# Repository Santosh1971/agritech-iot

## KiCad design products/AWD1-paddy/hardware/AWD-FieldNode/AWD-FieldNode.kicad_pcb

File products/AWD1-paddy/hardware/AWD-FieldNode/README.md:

# AWD field node v0.3: segmented capacitive level strip on a 2-layer board

This board is the paddy AWD (alternate wetting and drying) field node. It is a T-shaped, **2-layer** PCB (v0.1 was 4 layers).

- **Head:** 40 × 60 mm, inside a sealed 50 mm PVC end cap.
  - **Front:** ESP32-S3-MINI-1, ISC-SX1262-B LoRa module (same module and pin map as WPC), SMA, the touch series resistors.
  - **Back:** power: battery connector J3 (LiFePO4 14500), magnetic-socket connector J4, charger, LDO, fuse, reverse protection, USB ESD.
- **Strip:** 16 × 300 mm, pushed into the AWD tube.
  - 12 sensing pads, 6 × 18 mm on a 20 mm pitch, covering +7 to −17 cm, plus a dry reference pad (REF) above them.
  - One 12 × 20 mm GND water-return pad at the bottom.

The node reports to a WPC-style Master over LoRa at 866 MHz.

## Why 2 layers works for the strip

| Layer | What is on it |
|---|---|
| F.Cu | Pads in the left column. On the right, a **staircase** of 0.15 mm sense lanes, each between two 0.15 mm **GND guard traces** (0.15 mm gaps). Each lane runs straight down and steps left into its pad; the guard on its left ends just above that pad in a via to the back GND. |
| B.Cu | GND: 25 % hatch behind the pads, solid behind the lanes. No routing allowed on the back of the strip. |

- **Water rises from the bottom, and every lane runs only above its own pad.** A pad is always wet before any part of its own lane is, so water touching a lane can only make an already-wet pad read wetter.
- **The guards stop crosstalk** between a wet lower pad's lane and a dry higher pad's lane, the job the inner GND planes did in v0.1.
- **Cost:** a 2-layer board, HASL finish and no impedance control costs roughly a third to a half of the 4-layer ENIG board (estimate, check the quote).
- **To verify on the bench before the field:** in a water tube, check that a dry pad's reading does not move when the pads below it go under water.

The v0.1 4-layer board and its Gerbers are kept in `archive/v0.1-4layer/` for comparison.

## Status (v0.3, 2026-11-15)

| Item | State |
|---|---|
| Schematic | v0.3: v0.2 field charging + new touch-channel order. 66 parts. **ERC: 0 errors, 0 warnings.** |
| PCB | Generated by `tools/build.sh` (placement, strip, Freerouting, GND stitching, silkscreen). **DRC at every severity: 0 violations, 0 unconnected, schematic parity clean** (kicad-cli 9.0.7). |
| Fab | `fab/`: Gerbers + drills (`AWD-FieldNode-gerbers.zip`, **order this**), BOM, CPL (both sides), schematic PDF, 1:1 prints of top and bottom, STEP, renders. Regenerate with `zsh tools/fab.sh`. |
| Enclosure | Strip slot and gland widened for the 16 mm strip (`enclosure/awd_enclosure.scad`, STLs re-exported). |
| Open | The front-shell light window only sits over D1 (status LED). D2/D3 (charge LEDs) are 3.5–7 mm to its right: widen the window, or move them, when the magnetic-socket hole is added to the shell. J3 (battery) is now on the back-right corner, so the AA-holder lead runs there. |

### Changes from v0.1/v0.2

- 4 layers → 2 layers; strip 10 → 16 mm; pads 8 → 6 mm wide; ENIG → HASL.
- **The touch bus is drawn by the generator, not the autorouter:** each ESP32 touch pin goes through a via to B.Cu, runs as a ladder straight down under the LoRa module (F.Cu above it is a solid GND pour), and steps back up into its 510 Ω resistor. Channels follow the pads, so nothing crosses: **REF = T13/IO13, P1 = T12/IO12 … P12 = T1/IO1. Firmware must use this map.**
- **SMA J1:** v0.1 placed it with its pads running 1.4 mm past the board edge. In the footprint the connector body face is where the pads end (2.54 mm from the origin), so v0.3 puts the pad ends 0.3 mm inside the edge.
- The power block moved to the back so the 13 touch traces have the front-left corner of the head to themselves.
- No top-layer tracks under the LoRa module: F.Cu there is solid GND under the radio, and only the touch bus passes, on B.Cu below that pour. The battery connector J3 moved to the back-right corner to make room. No tracks or vias within 0.6 mm of the head edges.
- Antenna feed: 1.0 mm grounded coplanar line, 0.2 mm gap to the F.Cu pour, solid GND behind. It is about 11 mm long (λ/16 at 866 MHz in FR4), so no impedance control is ordered.

## Pin map (ESP32-S3)

| Function | GPIO |
|---|---|
| Touch T13 → REF pad | IO13 |
| Touch T12 → P1, T11 → P2 … T1 → P12 (Pn = IO(13 − n)) | IO12 … IO1 |
| VBUS_DET (charger present, deep-sleep wake), to TP1 | IO14 |
| VBAT_ADC (ADC2_CH4) / VBAT_EN | IO15 / IO16 |
| LoRa DIO1 / BUSY / RST | IO17 / IO18 / IO21 |
| LoRa NSS / SCK / MOSI / MISO | IO39 / IO40 / IO41 / IO42 |
| LED | IO38 |
| PAIR/BOOT button | IO0 |
| USB D−/D+ and UART0 | J2 (1.27 mm pogo/header) |

## v0.2 power: charging in the field through a magnetic socket

v0.1 put the 14500 straight onto the 3V3 rail with no charger, so the box had to be opened to charge the cell. v0.2 adds the same charging block as TH2:

```
J4 magnetic socket (VBUS, D-, D+, GND) -> F1 0.5 A polyfuse -> VBUS -> U3 CN3058E (0.31 A, 3.6 V CV) -> VBAT
J3 14500 -> Q1 reverse protection -> VBAT -> U4 RT9080-33 (2 uA Iq) -> +3V3
```

- **The LDO is now required:** while charging, VBAT sits at 3.6 V, which is the ESP32-S3's absolute maximum.
- **Battery sense:** R4 now measures **VBAT** (before the LDO), not +3V3.
- **USB:** J4's D−/D+ join the native-USB lines already on J2, through U5 (USBLC6 ESD protection). The node can be flashed through the magnetic cable without opening the box.
- **Charge LEDs:** D2 red (charging) and D3 green (full) run off VBUS. Place them under, or next to, the front-shell light window.
- **Charger detect:** VBUS_DET (R12/R13 divider to IO14, an RTC GPIO) wakes the S3 when the cable is clipped on.
- **Enclosure:** the magnetic socket needs its own wall hole, because the side hole is used by the SMA. That waits until the socket's flange size is known (ElectronifyIndia 4-pin flanged for prototypes, HytePro M826 waterproof for production). It goes in the shared AWD/TH shell.

## AWD thresholds

| Action | Condition |
|---|---|
| Pump OFF (+5 cm) | P2 wet |
| Pump ON (−15 cm) | P11 dry |
| SOIL line (0 cm) | Printed on both faces as the installation depth mark |

## Regenerate

Everything is generated from `tools/design.py` (parts, nets, strip geometry).

```bash
cd products/AWD1-paddy/hardware/AWD-FieldNode
zsh tools/build.sh      # schematic + ERC, board, Freerouting (retried until DRC is clean), stitching, silkscreen
zsh tools/fab.sh        # fab/: gerbers, drills, BOM, CPL, PDFs, STEP, renders
```

`build.sh` rebuilds the board from scratch every time, so any hand edits in KiCad are lost: make changes in `design.py` / `gen_pcb.py` instead. Freerouting 1.9.0 is expected at `~/Applications/freerouting/freerouting-1.9.0.jar`.

## Fab notes

- **2 layers, 1.6 mm FR4, HASL lead-free, green mask both sides, vias tented.** Minimum track/gap 0.15 mm, minimum drill 0.3 mm.
- Parts on **both sides**: power block on the back. For JLC assembly choose two-sided, or hand-solder the back.
- The pads have **no mask opening**. Below the neck the strip carries no exposed copper.
- After assembly, dip-coat the strip in 2-part epoxy or PU, 100–200 µm thick, and seal the routed edges.

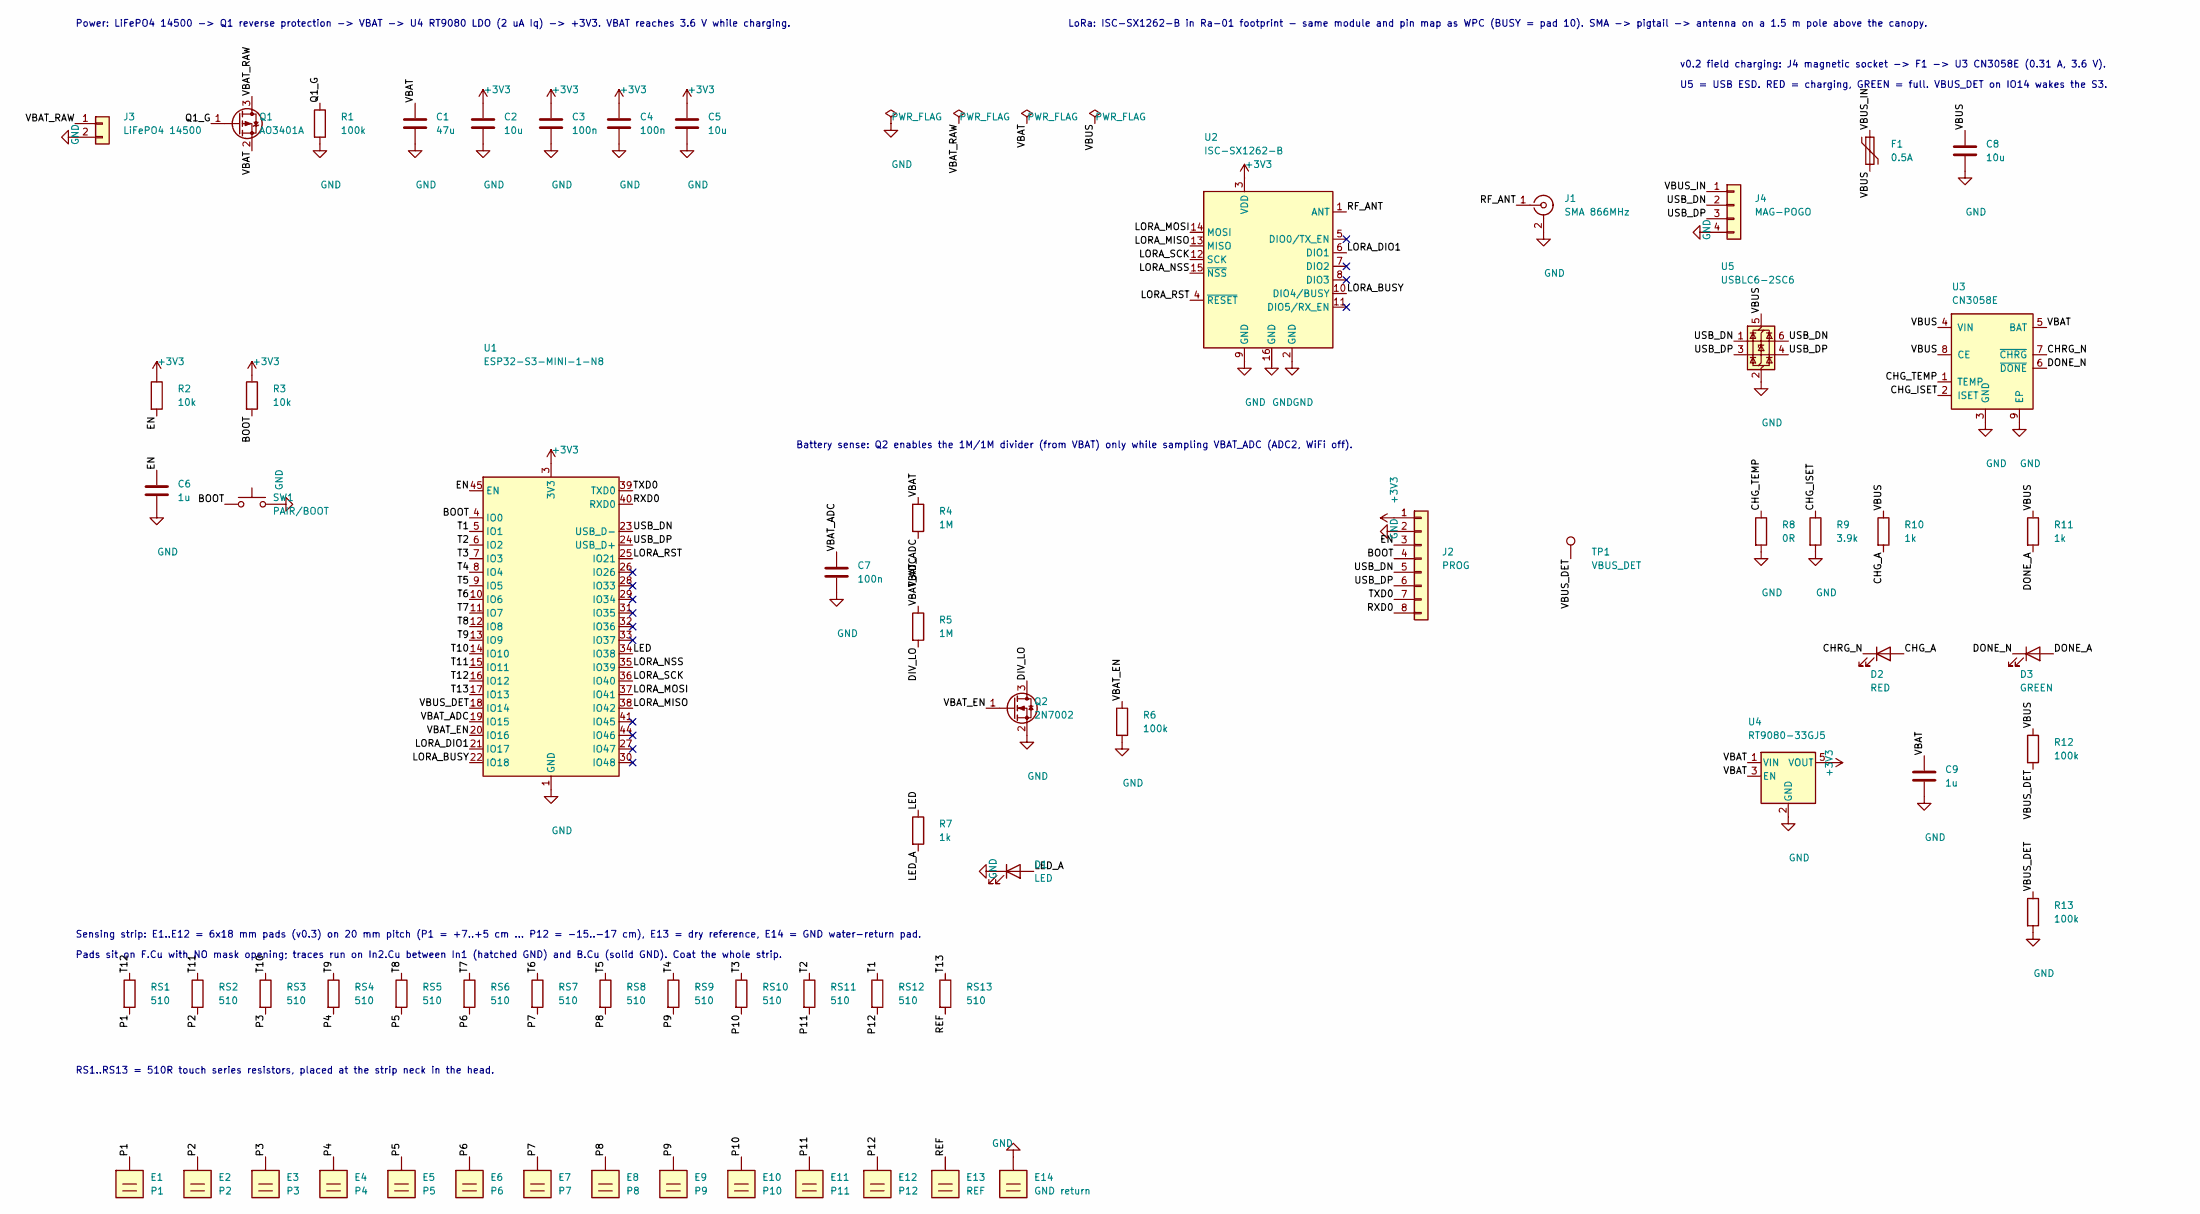
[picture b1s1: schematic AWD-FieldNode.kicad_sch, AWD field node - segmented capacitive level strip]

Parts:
C1: 47u; C_1206_3216Metric
C2, C5, C8: 10u; C_0805_2012Metric
C3, C4, C7: 100n; C_0603_1608Metric
C6, C9: 1u; C_0603_1608Metric
D1: LED; LED_0603_1608Metric
D2: RED; LED_0603_1608Metric
D3: GREEN; LED_0603_1608Metric
E1: P1; SensePad_6x18mm
E2: P2; SensePad_6x18mm
E3: P3; SensePad_6x18mm
E4: P4; SensePad_6x18mm
E5: P5; SensePad_6x18mm
E6: P6; SensePad_6x18mm
E7: P7; SensePad_6x18mm
E8: P8; SensePad_6x18mm
E9: P9; SensePad_6x18mm
E10: P10; SensePad_6x18mm
E11: P11; SensePad_6x18mm
E12: P12; SensePad_6x18mm
E13: REF; SensePad_6x12mm
E14: GND return; ReturnPad_12x20mm
F1: 0.5A; Fuse_1206_3216Metric
J1: SMA 866MHz; SMA_Amphenol_132289_EdgeMount
J2: PROG; PinHeader_1x08_P1.27mm_Vertical
J3: LiFePO4 14500; JST_PH_S2B-PH-SM4-TB_1x02-1MP_P2.00mm_Horizontal
J4: MAG-POGO; JST_PH_S4B-PH-SM4-TB_1x04-1MP_P2.00mm_Horizontal
Q1: AO3401A; SOT-23
Q2: 2N7002; SOT-23
R1, R6, R12, R13: 100k; R_0603_1608Metric
R2, R3: 10k; R_0603_1608Metric
R4, R5: 1M; R_0603_1608Metric
R7, R10, R11: 1k; R_0603_1608Metric
R8: 0R; R_0603_1608Metric
R9: 3.9k; R_0603_1608Metric
RS1, RS2, RS3, RS4, RS5, RS6, RS7, RS8, RS9, RS10, RS11, RS12, RS13: 510; R_0402_1005Metric
SW1: PAIR/BOOT; SW_SPST_TL3342
TP1: VBUS_DET; TestPoint_Pad_D1.5mm
U1: ESP32-S3-MINI-1-N8; ESP32-S2-MINI-1
U2: ISC-SX1262-B; Ai-Thinker-Ra-01-LoRa
U3: CN3058E; SOIC-8-1EP_3.9x4.9mm_P1.27mm_EP2.41x3.3mm
U4: RT9080-33GJ5; SOT-23-5
U5: USBLC6-2SC6; SOT-23-6

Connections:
+3V3: C2.1, C3.1, C4.1, C5.1, J2.1, R2.1, R3.1, U1.3 (3V3), U2.3 (VDD), U4.5 (VOUT)
/BOOT: J2.4, R3.2, SW1.1, U1.4 (IO0)
/CHG_A: D2.2 (A), R10.2
/CHG_ISET: R9.1, U3.2 (ISET)
/CHG_TEMP: R8.1, U3.1 (TEMP)
/CHRG_N: D2.1 (K), U3.7 (~CHRG)
/DIV_LO: Q2.3 (D), R5.2
/DONE_A: D3.2 (A), R11.2
/DONE_N: D3.1 (K), U3.6 (~DONE)
/EN: C6.1, J2.3, R2.2, U1.45 (EN)
/LED: R7.1, U1.34 (IO38)
/LED_A: D1.2 (A), R7.2
/LORA_BUSY: U1.22 (IO18), U2.10 (DIO4/BUSY)
/LORA_DIO1: U1.21 (IO17), U2.6 (DIO1)
/LORA_MISO: U1.38 (IO42), U2.13 (MISO)
/LORA_MOSI: U1.37 (IO41), U2.14 (MOSI)
/LORA_NSS: U1.35 (IO39), U2.15 (~NSS)
/LORA_RST: U1.25 (IO21), U2.4 (~RESET)
/LORA_SCK: U1.36 (IO40), U2.12 (SCK)
/P1: E1.1, RS1.2
/P2: E2.1, RS2.2
/P3: E3.1, RS3.2
/P4: E4.1, RS4.2
/P5: E5.1, RS5.2
/P6: E6.1, RS6.2
/P7: E7.1, RS7.2
/P8: E8.1, RS8.2
/P9: E9.1, RS9.2
/P10: E10.1, RS10.2
/P11: E11.1, RS11.2
/P12: E12.1, RS12.2
/Q1_G: Q1.1 (G), R1.1
/REF: E13.1, RS13.2
/RF_ANT: J1.1 (In), U2.1 (ANT)
/RXD0: J2.8, U1.40 (RXD0)
/T1: RS12.1, U1.5 (IO1)
/T2: RS11.1, U1.6 (IO2)
/T3: RS10.1, U1.7 (IO3)
/T4: RS9.1, U1.8 (IO4)
/T5: RS8.1, U1.9 (IO5)
/T6: RS7.1, U1.10 (IO6)
/T7: RS6.1, U1.11 (IO7)
/T8: RS5.1, U1.12 (IO8)
/T9: RS4.1, U1.13 (IO9)
/T10: RS3.1, U1.14 (IO10)
/T11: RS2.1, U1.15 (IO11)
/T12: RS1.1, U1.16 (IO12)
/T13: RS13.1, U1.17 (IO13)
/TXD0: J2.7, U1.39 (TXD0)
/USB_DN: J2.5, J4.2, U1.23 (USB_D-), U5.1 (I/O1), U5.6 (I/O1)
/USB_DP: J2.6, J4.3, U1.24 (USB_D+), U5.3 (I/O2), U5.4 (I/O2)
/VBAT: C1.1, C9.1, Q1.2 (S), R4.1, U3.5 (BAT), U4.1 (VIN), U4.3 (EN)
/VBAT_ADC: C7.1, R4.2, R5.1, U1.19 (IO15)
/VBAT_EN: Q2.1 (G), R6.1, U1.20 (IO16)
/VBAT_RAW: J3.1, Q1.3 (D)
/VBUS: C8.1, F1.2, R10.1, R11.1, R12.1, U3.4 (VIN), U3.8 (CE), U5.5 (VBUS)
/VBUS_DET: R12.2, R13.1, TP1.1, U1.18 (IO14)
/VBUS_IN: F1.1, J4.1
GND: C1.2, C2.2, C3.2, C4.2, C5.2, C6.2, C7.2, C8.2, C9.2, D1.1 (K), E14.1, J1.2 (Ext), J2.2, J3.2, J4.4, Q2.2 (S), R1.2, R6.2, R8.2, R9.2, R13.2, SW1.2, U1.1 (GND), U1.2 (GND), U1.42 (GND), U1.43 (GND), U1.46 (GND), U1.47 (GND), U1.48 (GND), U1.49 (GND), U1.50 (GND), U1.51 (GND), U1.52 (GND), U1.53 (GND), U1.54 (GND), U1.55 (GND), U1.56 (GND), U1.57 (GND), U1.58 (GND), U1.59 (GND), U1.60 (GND), U1.61 (GND), U1.62 (GND), U1.63 (GND), U1.64 (GND), U1.65 (GND), U2.2 (GND), U2.9 (GND), U2.16 (GND), U3.3 (GND), U3.9 (EP), U4.2 (GND), U5.2 (GND)

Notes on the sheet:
Power: LiFePO4 14500 -> Q1 reverse protection -> VBAT -> U4 RT9080 LDO (2 uA Iq) -> +3V3. VBAT reaches 3.6 V while charging.
LoRa: ISC-SX1262-B in Ra-01 footprint - same module and pin map as WPC (BUSY = pad 10). SMA -> pigtail -> antenna on a 1.5 m pole above the canopy.
Battery sense: Q2 enables the 1M/1M divider (from VBAT) only while sampling VBAT_ADC (ADC2, WiFi off).
v0.2 field charging: J4 magnetic socket -> F1 -> U3 CN3058E (0.31 A, 3.6 V).
U5 = USB ESD. RED = charging, GREEN = full. VBUS_DET on IO14 wakes the S3.
Sensing strip: E1..E12 = 6x18 mm pads (v0.3) on 20 mm pitch (P1 = +7..+5 cm ... P12 = -15..-17 cm), E13 = dry reference, E14 = GND water-return pad.
Pads sit on F.Cu with NO mask opening; traces run on In2.Cu between In1 (hatched GND) and B.Cu (solid GND). Coat the whole strip.
RS1..RS13 = 510R touch series resistors, placed at the strip neck in the head.

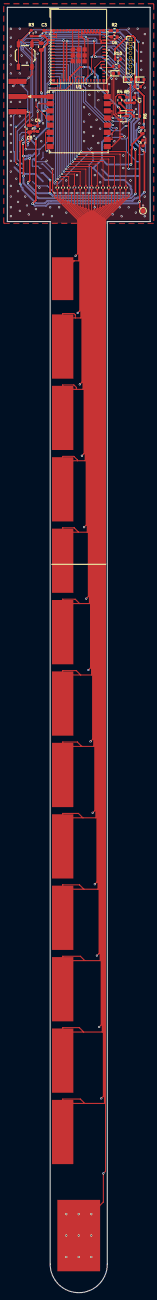
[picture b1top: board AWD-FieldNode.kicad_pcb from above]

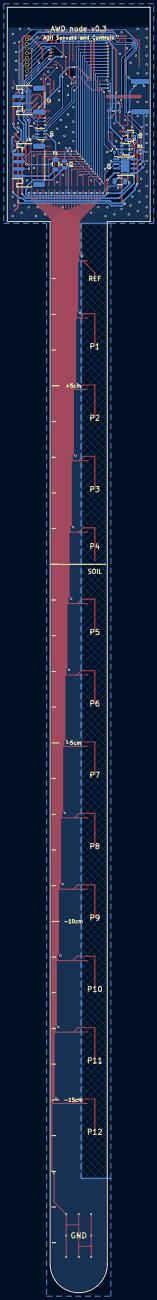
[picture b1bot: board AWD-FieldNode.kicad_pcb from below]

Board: 2 copper layers, 40.0 x 360.0 mm, 66 parts (13 on the bottom side), 59 nets.

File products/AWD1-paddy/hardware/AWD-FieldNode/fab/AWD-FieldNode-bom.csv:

"Reference","Value","Footprint","QUANTITY"
"C1","47u","Capacitor_SMD:C_1206_3216Metric","1"
"C2,C5,C8","10u","Capacitor_SMD:C_0805_2012Metric","3"
"C3,C4,C7","100n","Capacitor_SMD:C_0603_1608Metric","3"
"C6,C9","1u","Capacitor_SMD:C_0603_1608Metric","2"
"D1","LED","LED_SMD:LED_0603_1608Metric","1"
"D2","RED","LED_SMD:LED_0603_1608Metric","1"
"D3","GREEN","LED_SMD:LED_0603_1608Metric","1"
"F1","0.5A","Fuse:Fuse_1206_3216Metric","1"
"J1","SMA 866MHz","Connector_Coaxial:SMA_Amphenol_132289_EdgeMount","1"
"J2","PROG","Connector_PinHeader_1.27mm:PinHeader_1x08_P1.27mm_Vertical","1"
"J3","LiFePO4 14500","Connector_JST:JST_PH_S2B-PH-SM4-TB_1x02-1MP_P2.00mm_Horizontal","1"
"J4","MAG-POGO","Connector_JST:JST_PH_S4B-PH-SM4-TB_1x04-1MP_P2.00mm_Horizontal","1"
"Q1","AO3401A","Package_TO_SOT_SMD:SOT-23","1"
"Q2","2N7002","Package_TO_SOT_SMD:SOT-23","1"
"R1,R6,R12,R13","100k","Resistor_SMD:R_0603_1608Metric","4"
"R2,R3","10k","Resistor_SMD:R_0603_1608Metric","2"
"R4,R5","1M","Resistor_SMD:R_0603_1608Metric","2"
"R7,R10,R11","1k","Resistor_SMD:R_0603_1608Metric","3"
"R8","0R","Resistor_SMD:R_0603_1608Metric","1"
"R9","3.9k","Resistor_SMD:R_0603_1608Metric","1"
"RS1-RS13","510","Resistor_SMD:R_0402_1005Metric","13"
"SW1","PAIR/BOOT","Button_Switch_SMD:SW_SPST_TL3342","1"
"U1","ESP32-S3-MINI-1-N8","RF_Module:ESP32-S2-MINI-1","1"
"U2","ISC-SX1262-B","RF_Module:Ai-Thinker-Ra-01-LoRa","1"
"U3","CN3058E","Package_SO:SOIC-8-1EP_3.9x4.9mm_P1.27mm_EP2.41x3.3mm","1"
"U4","RT9080-33GJ5","Package_TO_SOT_SMD:SOT-23-5","1"
"U5","USBLC6-2SC6","Package_TO_SOT_SMD:SOT-23-6","1"

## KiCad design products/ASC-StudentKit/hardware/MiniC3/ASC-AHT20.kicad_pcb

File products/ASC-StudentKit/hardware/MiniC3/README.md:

# ASC Mini-C3 rev B: the low-cost Mini, shared with FG1

This is the cost-down Mini for the ASC Student Kit (2026-10-10). The same board is meant to become the next **FG1 (FlowGuard)**: it has FG1's flow input, relay, RTC and LEDs. It does not replace rev A (`../Mini`, ESP32-S3 module, 97 × 47 mm).

Two boards share one 100 × 100 order:

| Board | Size | What it is |
|---|---|---|
| **ASC-MiniC3** | 48 × 44 mm | Carrier for a plug-in ESP32-C3 Super Mini. It has a flow input, a 5 V pump driver, a 230 V relay, a DS1307 RTC, I2C and AUX terminals and four LEDs. |
| **ASC-AHT20** | 48 × 6 mm | A T/RH "sensor stick" on a 4-core cable, so the sensor sits outside the box and students can breathe on it |

**The panel (`fab/ASC-MiniC3-panel-gerbers.zip`, 98 × 98 mm, order this one):**
- It holds 4 Minis (2 × 2) and **2 sticks** underneath. FG1 builds don't need a stick.
- **No V-cut.** JLC charges extra for V-cut, so WhyPCB asked for routed slots instead.
- The boards are separated by **2 mm routed slots**, drawn as closed cut-outs in the board outline.
- The slots stop short at the panel edges and around the slot crossings, leaving small **plain tabs**: about 2 mm at the edges and 5 mm at the crossings.
- **No mouse bites:** WhyPCB says JLC may not accept them. To set them back, change `MOUSE_BITES` in `tools/panel.py`. Break the tabs with pliers or a nibbler and file the stubs flush.
- The zip also carries `ASC-MiniC3-panel-drawing.pdf` and `PANEL-README.txt` for the fab.
- Copper keeps ≥ 0.4 mm from every edge.
- **Price** (WhyPCB): ₹1,500 for 5 panels or ₹2,000 for 10, which is ₹50 per Mini at 10 panels. 98 × 98 stays inside their 100 × 100 price; they also accept up to 102 × 100.

## Status

| Item | State |
|---|---|
| Schematics | Both are generated from `tools/design.py` and `tools/design_aht20.py`. **ERC: 0 errors, 0 warnings** on both. |
| PCBs | Both are routed (Freerouting) with zones filled. **DRC at every severity: 0 violations, 0 unconnected, schematic parity clean** on both (kicad-cli 9.0.7). The panel's DRC shows 0 errors. |
| 230 V | **5.3 mm** measured from relay copper to anything else. The DRC rule in `ASC-MiniC3.kicad_dru` requires ≥ 5 mm. Inside the relay, coil and contacts are 9.6 mm apart. |
| Fab | Panel, Mini and stick Gerbers. JLC BOM/CPL for each board and for the panel (unique designators R1_1 … R1_4). Schematic PDFs, 1:1 prints and renders. Run `tools/fab.sh` to regenerate. |
| Costing | `costing.csv`: board plus stick about ₹267, full kit about ₹1,026 (IP-65-26, YF-S401 at ₹230, HF46F at ₹42, 3 standoffs) |
| Mounting | 3 × 4.2 mm holes, arranged in a triangle, for 5 mm nylon reverse-mount snap standoffs (Probots PRO5803, ₹9.40 at 50+). Each standoff's flat base sticks to the box floor with double-sided foam tape; the snap head goes through the PCB hole. This works in any box with a flat floor; the box's own bosses are not used. Enclosure: REI IP-65-26 (90 × 58 × 44). |

## 3D models

Our own parts have no 3D models in KiCad's library (the Phoenix terminals, the MSTBVA header and the JST-XH do). `tools/gen_3d.py` writes simple coloured STEP models for them into `ASC.3dshapes/` (boxes and cylinders sized from the datasheets):
- the Super Mini on its sockets;
- the tabbed CR2032 and the HF46F relay;
- the AHT20 and the snap standoffs (the standoffs show below the board).

`tools/apply_3d.py` attaches them to the routed boards without re-routing; `gen_pcb.py` and `panel.py` attach them automatically. `fab/ASC-MiniC3.step` and `fab/ASC-AHT20.step` are full board assemblies, for checking the fit in the enclosure.

## Pin map (ESP32-C3 Super Mini)

| GPIO | Function | Notes |
|---|---|---|
| IO0, IO1 | AUX A0, A1 | ADC1 inputs |
| IO3 | PUMP | ULN2003A channels 1 + 2 in parallel (about 0.9 V drop, so ~4 V at the pump). Off through reset. |
| IO4 | AUX D | 10 k pull-up. For DHT11/22 or a DS18B20 probe. |
| IO5 | FLOW | YF-S401 (5880 pulses per litre) or YF-S201 (450 per litre). Level-shifted by D2 + R6. |
| IO6, IO7 | SDA, SCL | DS1307 (0x68) and AHT20 (0x38). 4.7 k pull-ups to 3V3. |
| IO10 | STATUS LED | FG1 uses it as the WiFi/status LED |
| IO20 | RELAY | ULN2003A channel 3. This pin is UART0 RX, an input at boot, so the relay stays off while the board boots. ULN2003A inputs 4–7 are grounded, outputs 4–7 free. |
| IO2, IO8, IO9, IO21 | free | IO2/8/9 are strapping pins (IO8 = module LED, IO9 = BOOT). IO21 is UART0 TX. |

## Connectors

| Ref | Connector | Pins |
|---|---|---|
| J5 | I2C, 4-pole 3.5 mm screw terminal (top edge) | 3V3, GND, SCL, SDA. This is the AHT20 stick's order and the usual VIN GND SCL SDA module order. |
| J4 | FLOW (top right): one footprint, fit **either** a JST-XH 3-pin header (student bench: takes the YF-S401 plug) **or** a 3-pole 3.5 mm screw terminal (FG1 / field: long cable). | 5V (red), GND (black), SIG (yellow); silkscreen reads S G 5V, left to right |
| J3 | AUX, 5-pole 3.5 mm screw terminal (bottom edge) | 3V3, D, A0, A1, GND |
| J1 | PUMP, 2-pole 3.5 mm screw terminal (bottom edge) | P+ (5 V), P− (low side) |
| J6 | RELAY 230 V, pluggable 5.08 mm 2-pole MSTBVA header + plug (bottom right), the same family as FG1's relay connector | NO, COM. HF46F, 5 A 250 VAC, for a pump contactor coil. |

## Assembly markings (for hand soldering)

House style, as on the WPC and FG1 boards:
- **Labels:** every part has its reference and value on the top silkscreen: `R3 1K`, `R5 470E`, `U3 ULN2003`, `C1 220U`, `D3 YEL` and so on. R8 and R9 share one label, `R8 R9 4K7`.
- **Big parts:** the relay and coin-cell labels sit inside their outlines, where the part goes.
- **Pin 1:** a **1** marks pin 1 of each IC (U2 DS1307, U3 ULN2003, the AHT20).
- **Anodes:** a **+** marks the anode of every LED and of D2.
- **LED colours:** PUMP and RLY yellow, STATUS red, FLOW yellow-green. FLOW runs from 3.3 V, too low for an emerald green LED. The Super Mini's own blue LED (GPIO8) is the WiFi-status LED in firmware. The electrolytic and the coin cell carry their own + marks.
- **LED size:** the LEDs are **1206** (bigger pads, as on WPC).
- **Back:** "ASC Mini-C3 rev B / Agri Sensors and Controls Oct 2026".

`gen_pcb.py` places the labels automatically, clear of pads, part bodies and each other (`ASSEMBLY_VALUE`, `LABEL_INSIDE` and `MARKS` in the design file). The LED block is laid out by hand in `silk()`.

## LEDs (seen through the clear lid)

| LED | How it's driven |
|---|---|
| PUMP (red) | Hardware: on the pump driver |
| FLOW (yellow) | Hardware: blinks with every flow pulse |
| STATUS (green) | GPIO10 |
| RELAY (blue) | Hardware: across the relay coil |

## Moving FG1 onto this board

1. **Firmware.** FG1 runs on a classic ESP32 today (`esp32dev`). It needs a C3 build with these pins: RELAY IO20, FLOW IO5, I2C IO6/IO7, status LED IO10.
2. **Flow LED.** It no longer needs a GPIO, so FG1's `FLOW_SENSOR_LED_PIN` goes away.
3. **Flow sensor.** Set `DEFAULT_PULSES_PER_LITER` to suit the sensor: 450 for a YF-S201, 5880 for a YF-S401.
4. **Power.** In the field, FG1 runs from a 5 V / 1 A USB-C charger plugged into the Super Mini.
5. **Relay.** The relay is an HF46F (5 A), not FG1's SRD (10 A). That is ample for a contactor coil. The SRD's COM pin sits between its two coil pins, which made 5 mm clearance impossible on a 48 mm board.

## Check before ordering

1. **Super Mini footprint.** Print `fab/ASC-MiniC3-print-1to1.pdf` at 100 % and lay a real Super Mini on it. The rows should be 15.24 mm apart. The silkscreen marks IO5 and 5V at the USB end and IO21 and IO0 at the far end, so a mirrored module is easy to see.
2. **Tabbed CR2032.** The two + legs are 15.2 mm apart. The − leg offset of 4.0 mm is a guess, so measure one cell.
   - **Alternative:** a replaceable cell in a CR2032 holder ([Rajiv Electronics](https://rajivelectronics.com/product/cr2032-3v-pcb-mount-vertical-battery-holder), ₹11.80).
   - The Rajiv holder (photo, SKU RBH-2) is a vertical holder with **3 pins**. A different holder's datasheet shows 2 pins 20.0 mm apart, so the layout varies by maker.
   - Its pin positions may or may not match the tabbed cell's pads. **Measure a sample before ordering.**
   - If they differ, its pads can be added next to the tabbed cell's, the same way the flow connector takes either part.
3. **YF-S401 plug order.** The board expects 5V (red) on pin 1, GND (black) in the middle and SIG (yellow) on pin 3. This follows AM Electronics' listing and photo. Check one plug: red must land on the pin next to the 5V label.
4. **HF46F footprint.** It is the same footprint as rev A (Hongfa datasheet). Push a real relay through a 1:1 print.
5. **AHT20 footprint.** It follows the ASAIR datasheet V1.0.03, figure 8: 0.8 × 0.5 mm pads at 1.0 mm pitch, rows 2.0 mm apart. Pins: 2 VDD, 3 SCL, 4 SDA, 5 GND.
6. **Assembly on the panel.** JLC assembly normally wants 5 mm rails, which would make the panel 96 × 110 mm. Either assemble by hand (every passive is 0805; the AHT20 needs hot air or a stencil) or ask WhyPCB whether they can place parts on a panel with no rails.
7. **USB power.** The pump (0.2–0.3 A), the relay coil (~70 mA) and the C3 (up to ~350 mA) all run from USB 5 V. Use a 1 A charger.

## Regenerate

```bash
cd products/ASC-StudentKit/hardware/MiniC3
KP=/Applications/KiCad/KiCad.app/Contents/Frameworks/Python.framework/Versions/Current/bin/python3
for d in design design_aht20; do
  DESIGN=$d python3 tools/gen_sch.py      # schematic, ASC.kicad_sym, tools/netlist-<PROJECT>.json
  DESIGN=$d $KP tools/gen_pcb.py          # placed board (plus the locked 230 V tracks)
  DESIGN=$d $KP tools/route.py            # Freerouting 1.9 (~/Applications/freerouting), then zone fill
done
kicad-cli pcb drc --schematic-parity --severity-all -o /tmp/drc.rpt ASC-MiniC3.kicad_pcb
$KP tools/panel.py                        # panel/ASC-MiniC3-panel.kicad_pcb
zsh tools/fab.sh                          # fab/
```

Freerouting is not deterministic. If DRC reports unconnected items, run `gen_pcb.py` and `route.py` again; a clean result usually comes within a few runs.

How the routing script handles the special nets:
- The two 230 V tracks are drawn and locked by `gen_pcb.py`. Freerouting cannot place them, because the terminal's own pins are closer together than the 5 mm class clearance.
- The GND pours are taken out of the DSN export, so GND is also routed as tracks.
- The no-pour areas are taken out of the export too, because the exporter would turn them into full keep-outs.

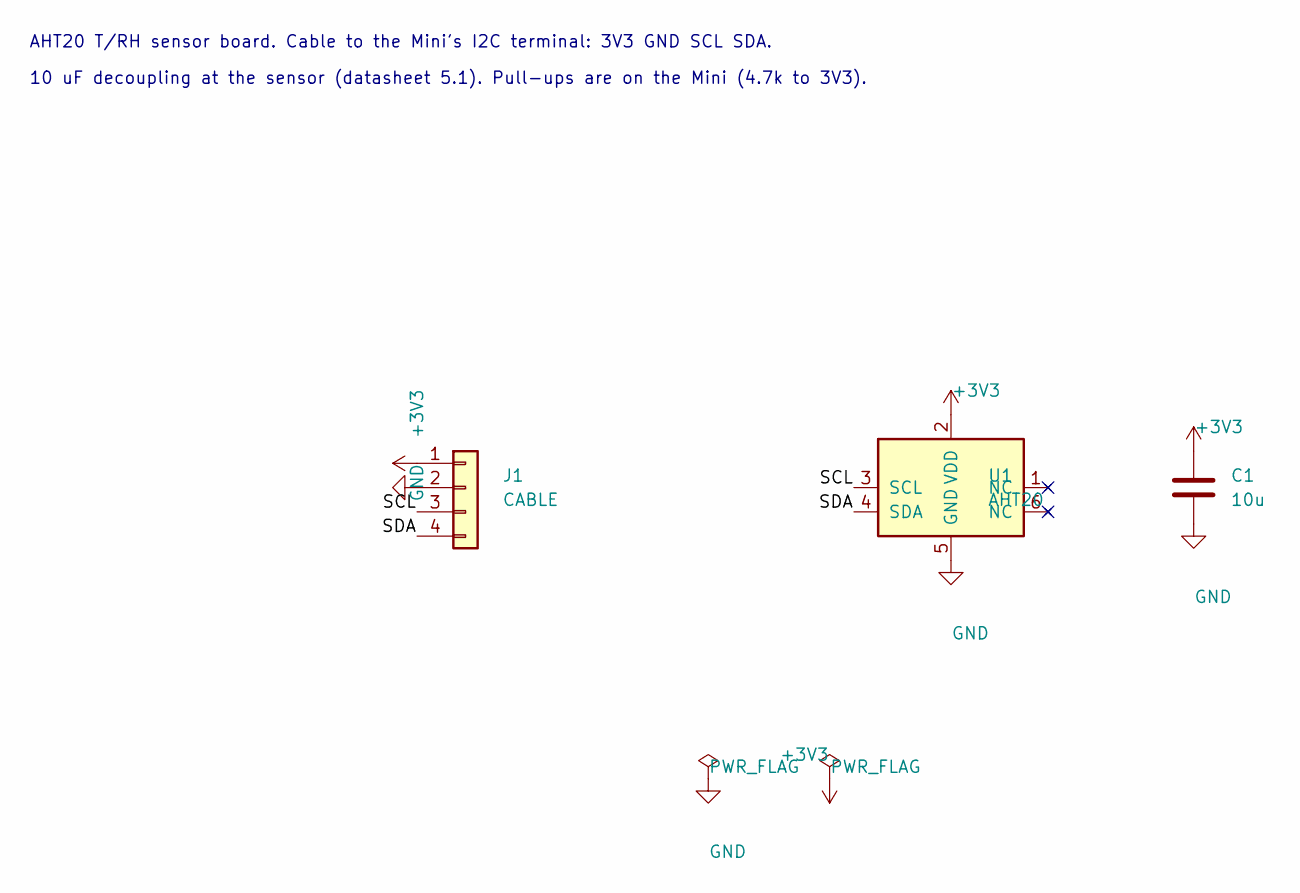
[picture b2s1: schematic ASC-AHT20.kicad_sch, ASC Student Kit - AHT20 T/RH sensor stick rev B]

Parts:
C1: 10u; C_0805_2012Metric
J1: CABLE; PinHeader_1x04_P2.54mm_Vertical
U1: AHT20; Aosong_AHT20_DFN-6_3x3mm

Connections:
+3V3: C1.1, J1.1, U1.2 (VDD)
/SCL: J1.3, U1.3 (SCL)
/SDA: J1.4, U1.4 (SDA)
GND: C1.2, J1.2, U1.5 (GND)

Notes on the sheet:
AHT20 T/RH sensor board. Cable to the Mini's I2C terminal: 3V3 GND SCL SDA.
10 uF decoupling at the sensor (datasheet 5.1). Pull-ups are on the Mini (4.7k to 3V3).

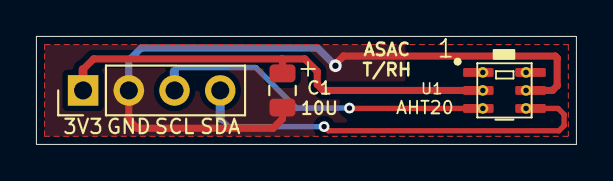
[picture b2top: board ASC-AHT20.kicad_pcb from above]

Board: 2 copper layers, 30.0 x 6.0 mm, 3 parts (0 on the bottom side), 4 nets.

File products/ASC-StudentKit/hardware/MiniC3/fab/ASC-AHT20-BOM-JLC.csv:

Comment,Designator,Footprint,LCSC Part #
10u,C1,C_0805_2012Metric,C15850
AHT20,U1,Aosong_AHT20_DFN-6_3x3mm,C2757850

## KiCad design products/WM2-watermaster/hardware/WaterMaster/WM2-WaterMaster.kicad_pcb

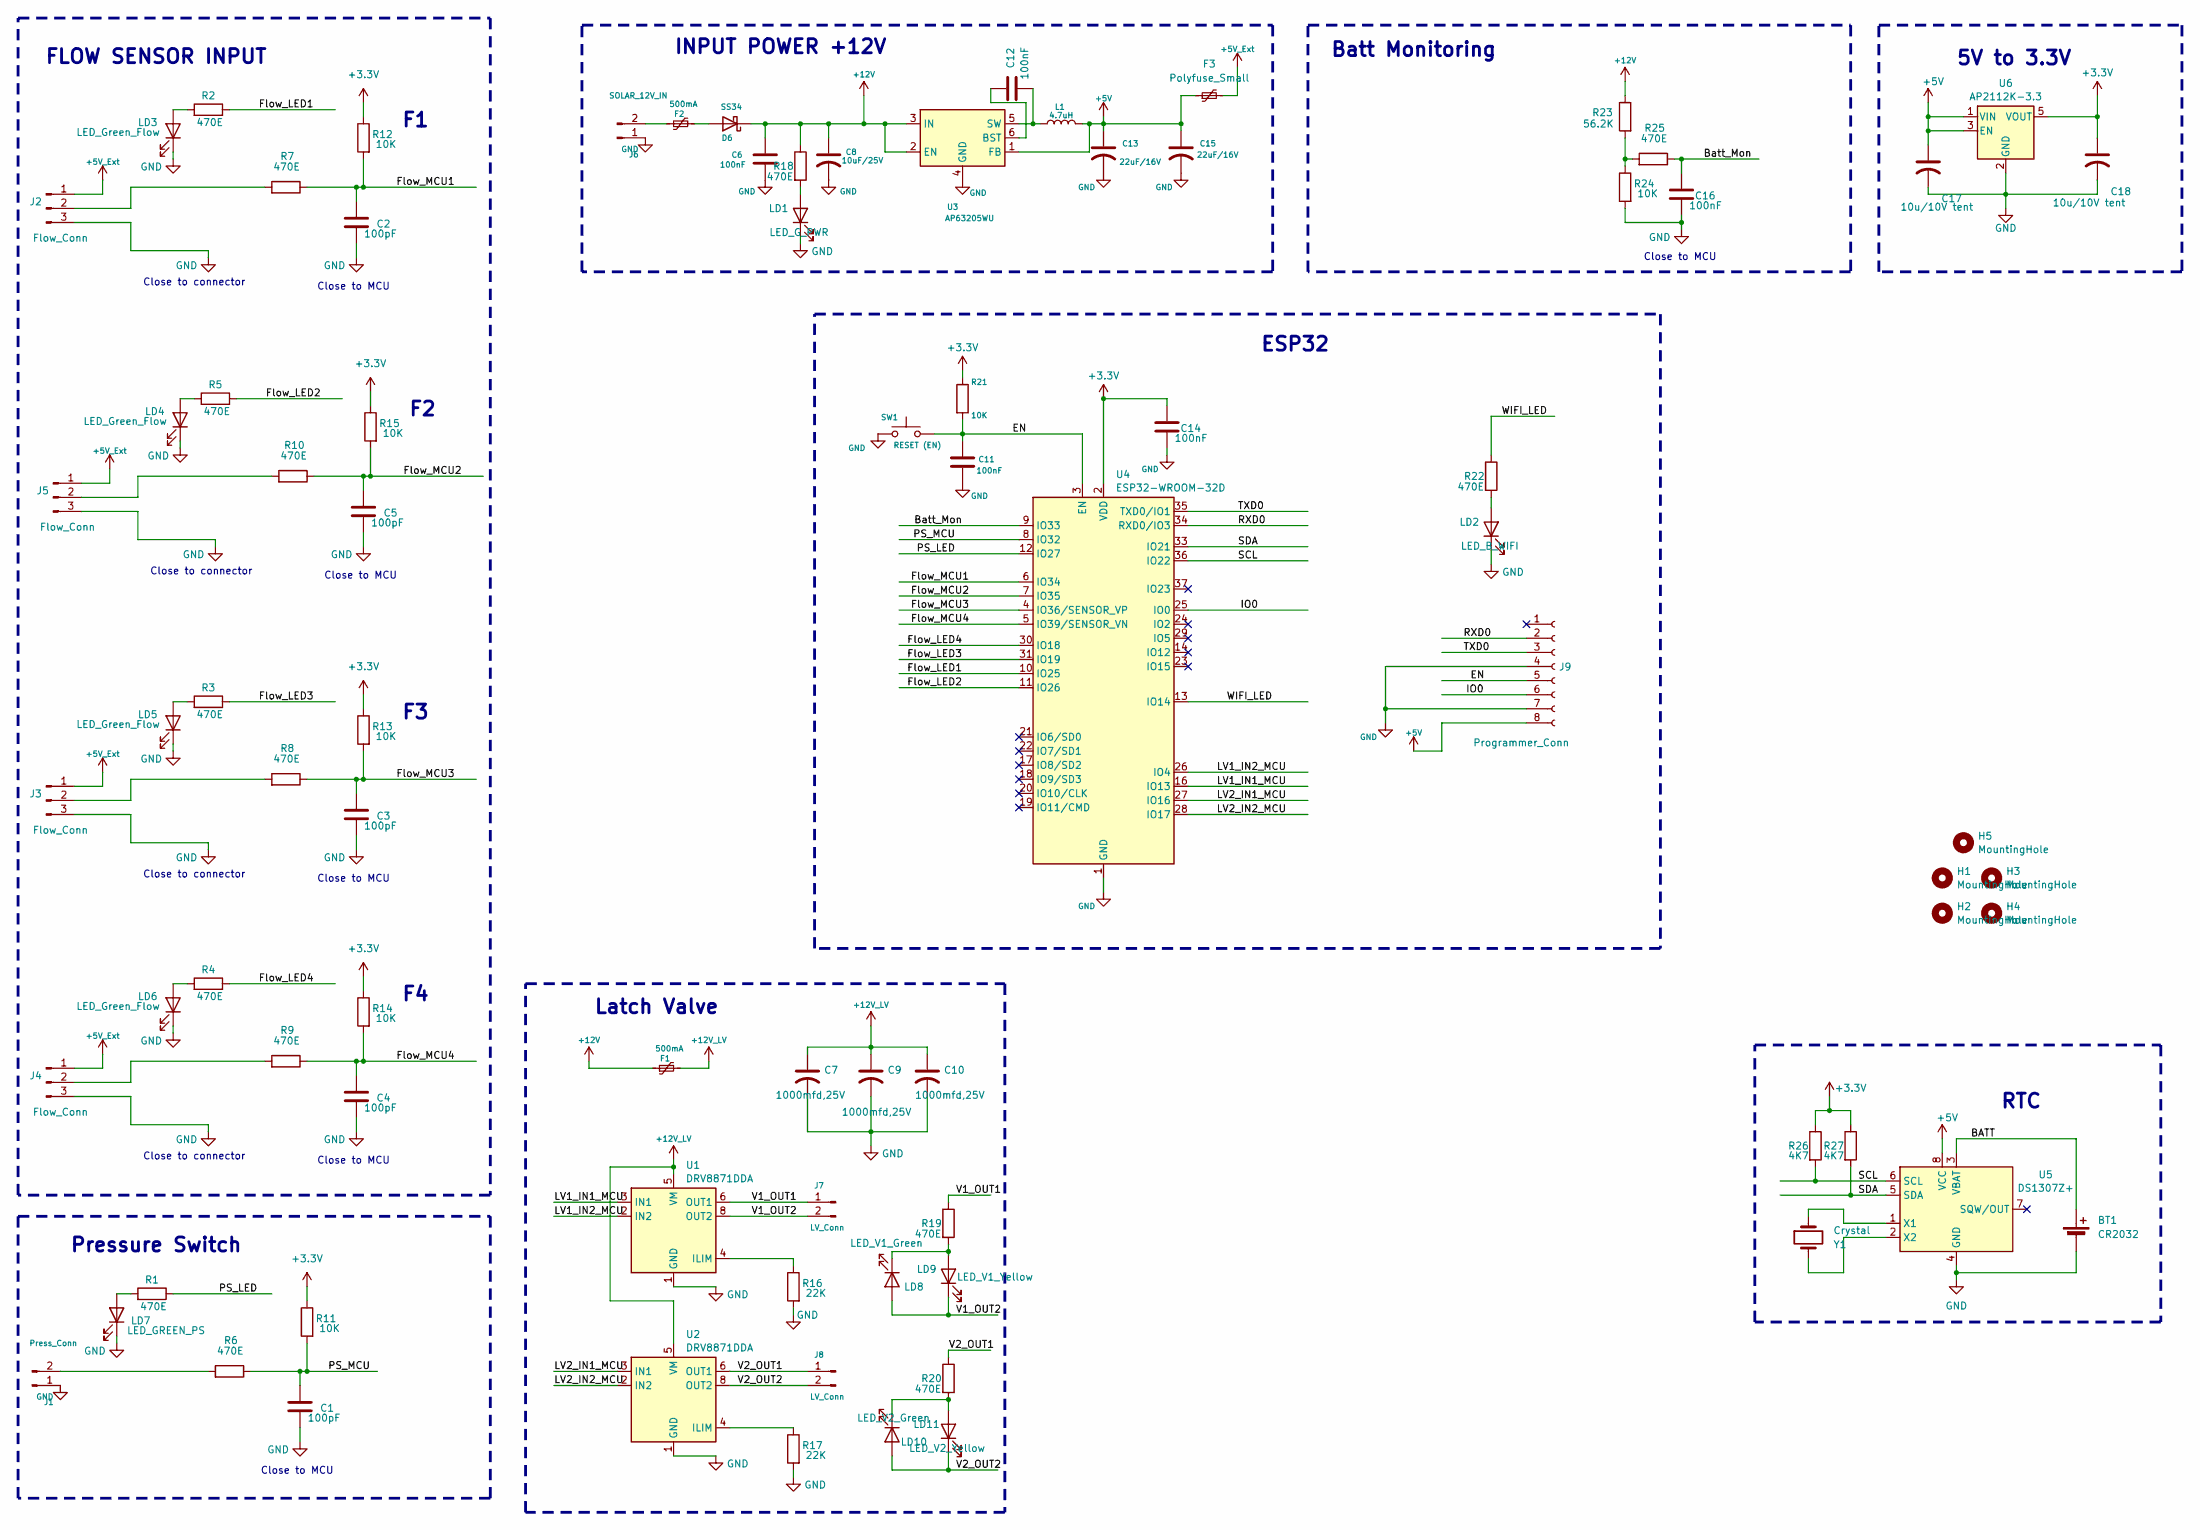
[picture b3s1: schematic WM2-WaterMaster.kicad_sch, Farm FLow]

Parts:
BT1: CR2032; BatteryHolder_MYOUNG_BS-07-A1BJ001_CR2032
C1, C2, C3, C4, C5: 100pF; C_0805_2012Metric
C6, C11, C12, C14, C16: 100nF; C_0805_2012Metric
C7, C9, C10: 1000mfd,25V; CP_Radial_D10.0mm_P2.50mm_P5.00mm
C8: 10uF/25V; C_1206_3216Metric_Pad1.33x1.80mm_HandSolder
C13, C15: 22uF/16V; C_1206_3216Metric_Pad1.33x1.80mm_HandSolder
C17, C18: 10u/10V tent; C_0805_2012Metric
D6: SS34; D_SMA
F1, F2: 500mA; L_1206_3216Metric
F3: Polyfuse_Small; L_1206_3216Metric
H1, H2, H3, H4, H5: MountingHole; MountingHole_4.5mm
J1: Press_Conn; PhoenixContact_MSTBA_2,5_2-G-5,08_1x02_P5.08mm_Horizontal
J2, J3, J4, J5: Flow_Conn; PhoenixContact_MSTBVA_2,5_3-G-5,08_1x03_P5.08mm_Vertical
J6: SOLAR_12V_IN; PhoenixContact_MSTBA_2,5_2-G-5,08_1x02_P5.08mm_Horizontal
J7, J8: LV_Conn; PhoenixContact_MSTBA_2,5_2-G-5,08_1x02_P5.08mm_Horizontal
J9: Programmer_Conn; JST_XH_B8B-XH-AM_1x08_P2.50mm_Vertical
L1: 4.7uH; L_Neosid_Ms85T
LD1: LED_G_PWR; C_1206_3216Metric
LD2: LED_B_WIFI; C_1206_3216Metric
LD3, LD4, LD5, LD6: LED_Green_Flow; C_1206_3216Metric
LD7: LED_GREEN_PS; C_1206_3216Metric
LD8: LED_V1_Green; C_1206_3216Metric
LD9: LED_V1_Yellow; C_1206_3216Metric
LD10: LED_V2_Green; C_1206_3216Metric
LD11: LED_V2_Yellow; C_1206_3216Metric
R1, R2, R3, R4, R5, R6, R7, R8, R9, R10, R18, R19, R20, R22, R25: 470E; R_0805_2012Metric
R11, R12, R13, R14, R15, R21, R24: 10K; R_0805_2012Metric
R16, R17: 22K; R_0805_2012Metric
R23: 56.2K; R_0805_2012Metric
R26, R27: 4K7; R_0805_2012Metric
SW1: RESET (EN); SW_Tactile_SPST_NO_Straight_CK_PTS636Sx25SMTRLFS
U1, U2: DRV8871DDA; Texas_HTSOP-8-1EP_3.9x4.9mm_P1.27mm_EP2.95x4.9mm_Mask2.4x3.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
U3: AP63205WU; TSOT-23-6
U4: ESP32-WROOM-32D
U5: DS1307Z+; SOIC-8_3.9x4.9mm_P1.27mm
U6: AP2112K-3.3; SOT-23-5
Y1: Crystal; Crystal_C38-LF_D3.0mm_L8.0mm_Horizontal

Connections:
+3.3V: C14.1, C18.1, R11.1, R12.1, R13.1, R14.1, R15.1, R21.1, R26.1, R27.1, U4.2 (VDD), U6.5 (VOUT)
+5V: C13.1, C15.1, C17.1, F3.1, J9.8, L1.2, U3.1 (FB), U5.8 (VCC), U6.1 (VIN), U6.3 (EN)
+5V_Ext: F3.2, J2.1, J3.1, J4.1, J5.1
+12V: C6.1, C8.1, D6.1 (K), F1.1, R18.1, R23.1, U3.2 (EN), U3.3 (IN)
+12V_LV: C7.1, C9.1, C10.1, F1.2, U1.5 (VM), U2.5 (VM)
/BATT: BT1.1 (+), U5.3 (VBAT)
/Batt_Mon: C16.1, R25.1, U4.9 (IO33)
/EN: C11.1, J9.5, R21.2, SW1.1, U4.3 (EN)
/Flow_LED1: R2.1, U4.10 (IO25)
/Flow_LED2: R5.1, U4.11 (IO26)
/Flow_LED3: R3.1, U4.31 (IO19)
/Flow_LED4: R4.1, U4.30 (IO18)
/Flow_MCU1: C2.1, R7.1, R12.2, U4.6 (IO34)
/Flow_MCU2: C5.1, R10.1, R15.2, U4.7 (IO35)
/Flow_MCU3: C3.1, R8.1, R13.2, U4.4 (IO36/SENSOR_VP)
/Flow_MCU4: C4.1, R9.1, R14.2, U4.5 (IO39/SENSOR_VN)
/IO0: J9.6, U4.25 (IO0)
/LV1_IN1_MCU: U1.3 (IN1), U4.16 (IO13)
/LV1_IN2_MCU: U1.2 (IN2), U4.26 (IO4)
/LV2_IN1_MCU: U2.3 (IN1), U4.27 (IO16)
/LV2_IN2_MCU: U2.2 (IN2), U4.28 (IO17)
/PS_LED: R1.1, U4.12 (IO27)
/PS_MCU: C1.1, R6.1, R11.2, U4.8 (IO32)
/RXD0: J9.2, U4.34 (RXD0/IO3)
/SCL: R26.2, U4.36 (IO22), U5.6 (SCL)
/SDA: R27.2, U4.33 (IO21), U5.5 (SDA)
/TXD0: J9.3, U4.35 (TXD0/IO1)
/V1_OUT1: J7.1, R19.1, U1.6 (OUT1)
/V1_OUT2: J7.2, LD8.2 (A), LD9.1 (K), U1.8 (OUT2)
/V2_OUT1: J8.1, R20.1, U2.6 (OUT1)
/V2_OUT2: J8.2, LD10.2 (A), LD11.1 (K), U2.8 (OUT2)
/WIFI_LED: R22.1, U4.13 (IO14)
GND: BT1.2 (-), C1.2, C2.2, C3.2, C4.2, C5.2, C6.2, C7.2, C8.2, C9.2, C10.2, C11.2, C13.2, C14.2, C15.2, C16.2, C17.2, C18.2, J1.1, J2.3, J3.3, J4.3, J5.3, J6.1, J9.4, J9.7, LD1.1 (K), LD2.1 (K), LD3.1 (K), LD4.1 (K), LD5.1 (K), LD6.1 (K), LD7.1 (K), R16.2, R17.2, R24.2, SW1.2, U1.1 (GND), U1.7 (GND), U1.9 (GND), U2.1 (GND), U2.7 (GND), U2.9 (GND), U3.4 (GND), U4.1 (GND), U4.15 (GND), U4.38 (GND), U4.39 (GND), U5.4 (GND), U6.2 (GND)
unnamed: D6.2 (A), F2.2
unnamed: J1.2, R6.2
unnamed: J2.2, R7.2
unnamed: J3.2, R8.2
unnamed: J4.2, R9.2
unnamed: J5.2, R10.2
unnamed: F2.1, J6.2
unnamed: LD1.2 (A), R18.2
unnamed: LD2.2 (A), R22.2
unnamed: LD3.2 (A), R2.2
unnamed: LD4.2 (A), R5.2
unnamed: LD5.2 (A), R3.2
unnamed: LD6.2 (A), R4.2
unnamed: LD7.2 (A), R1.2
unnamed: LD8.1 (K), LD9.2 (A), R19.2
unnamed: LD10.1 (K), LD11.2 (A), R20.2
unnamed: R23.2, R24.1, R25.2
unnamed: R16.1, U1.4 (ILIM)
unnamed: R17.1, U2.4 (ILIM)
unnamed: C12.1, U3.6 (BST)
unnamed: C12.2, L1.1, U3.5 (SW)
unnamed: U5.1 (X1), Y1.1
unnamed: U5.2 (X2), Y1.2

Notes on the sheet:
RTC
INPUT POWER +12V
Close to MCU
ESP32
Close to connector
Latch Valve
Pressure Switch
FLOW SENSOR INPUT
5V to 3.3V
Batt Monitoring

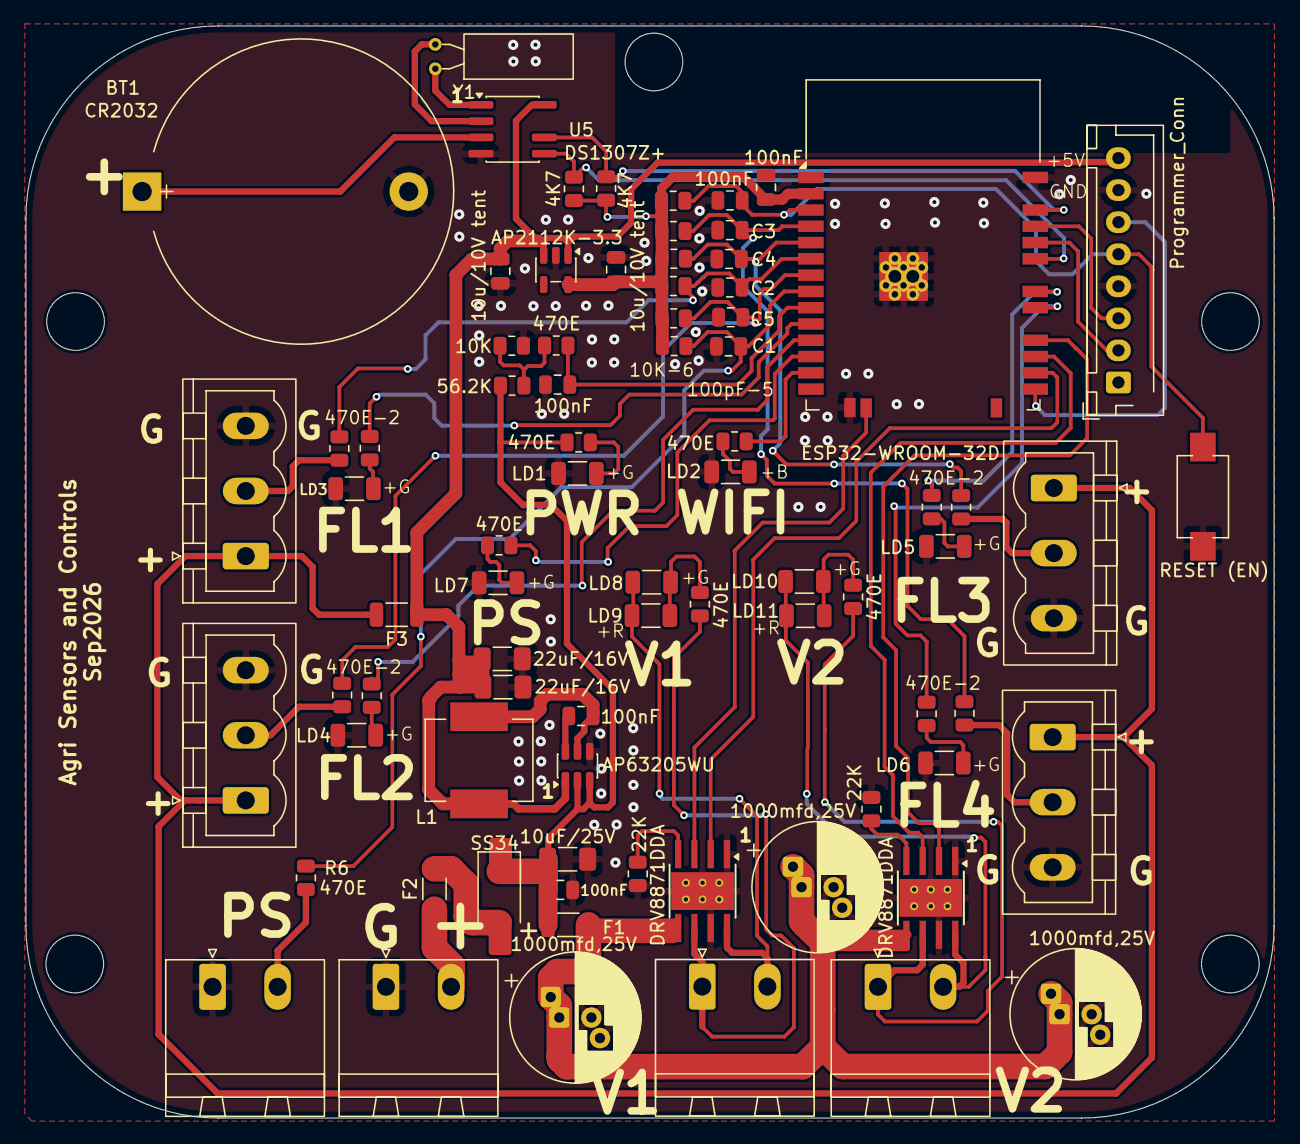
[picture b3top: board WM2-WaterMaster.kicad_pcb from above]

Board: 2 copper layers, 97.4 x 85.2 mm, 84 parts (0 on the bottom side), 56 nets.
